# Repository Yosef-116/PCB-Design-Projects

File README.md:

# PCB Design Class — Semester Projects

This repository contains all the PCB design projects completed throughout my PCB Design course, created using **KiCad**. The projects progressively build on each other, covering fundamental circuit concepts from simple switching circuits to microcontroller-based systems, culminating in a full AC to DC power converter as the final project.

---

## Project 01 — Mini Inverter

A half-bridge DC inverter circuit built around the **IR2153 self-oscillating half-bridge driver** and two **N-Channel Power MOSFETs (17A, 60V, TO-220)**. The circuit drives a transformer to produce an AC-like output from a DC battery source. LEDs are used for status indication. This was the introductory project, covering basic switching topologies, MOSFET gate driving, and transformer-coupled power circuits.

**Key components:** IR2153, N-Channel MOSFETs, transformer, LED, battery

---

## Project 02 — Arduino Nano + LCD Display

A microcontroller-based project integrating an **Arduino Nano v3.x** with an **NHD-0420E2Z LCD display** (4×20 character). The board routes power, data lines, and passive components between the module and the display. This project introduced working with microcontroller modules in KiCad, footprint assignment for through-hole and SMD packages, and multi-component PCB layout.

**Key components:** Arduino Nano v3.x, NHD-0420E2Z LCD, resistors, capacitors, battery

---

## Project 03 — 4-Digit 7-Segment LED Display Driver

A display driver circuit built around the **CC56-12SRWA** — a 4-digit, 7-segment super bright red LED display (common cathode). The schematic routes the segment and digit control lines from a battery-powered source. This project focused on understanding multi-digit display multiplexing, current-limiting resistors for each segment, and organizing a moderately complex schematic cleanly.

**Key components:** CC56-12SRWA (4-digit 7-segment display), resistors, single-cell battery

---

## Project 05 — LED Sequencer (CD4017 + NE555 Timer)

A classic LED chaser/sequencer circuit using the **CD4017 Johnson Counter** (10 decoded outputs) driven by the **NE555 timer IC** configured in astable mode. The 555 generates a clock signal that steps the 4017 through its outputs sequentially, lighting one LED at a time in a running pattern. This project explored timer circuits, clocking logic ICs, and the fundamentals of sequential logic on a PCB.

**Key components:** CD4017B, NE555 (SOIC-8), LEDs, resistors, capacitors, single-cell battery

---

## Project 06 — Sound-Activated Relay (Clap Switch)

A sound-triggered switching circuit that uses an **ECM microphone (AOM-6545P-R)** to pick up audio signals, amplified by the **OPA27GP precision op-amp**. The amplified signal is processed by a **74LS109 Dual JK Flip-Flop** to toggle a **PR12 5V relay (SPDT)** via a **TIP122 NPN Darlington transistor**. A trimmer potentiometer sets the sensitivity threshold. This project brought together analog signal conditioning, digital logic, and electromechanical output on one board.

**Key components:** AOM-6545P-R ECM mic, OPA27GP op-amp, 74LS109 JK flip-flop, TIP122 Darlington transistor, PR12-5V-360-1C relay, 1N4001 flyback diode, trimmer potentiometer

---

## Project 07 — USB-C Powered LED Dimmer

A variable LED brightness circuit powered through a **USB Type-C receptacle (6-pin, power-only)**. The circuit uses a **BD140 PNP power transistor** as the main switch, a **TL431D shunt voltage regulator** for reference, and a **potentiometer (RK163)** to allow manual dimming control. A fast-switching diode (1N4148WT) handles transient protection. This project introduced USB-C power input integration and analog control of LED brightness through transistor biasing.

**Key components:** USB_C_Receptacle_PowerOnly_6P, BD140 PNP transistor, TL431D shunt regulator, RK163 potentiometer, 1N4148WT diode, LED, resistors

---

## Project 08 — Stereo Audio Amplifier (LA4440)

A two-channel stereo audio amplifier board built around the **LA4440-E**, a Class AB 2-channel amplifier IC in a 14-pin SIP package (by onsemi). The board includes the necessary input/output coupling capacitors and resistor network as specified in the datasheet. This project covered audio amplifier PCB layout considerations such as ground planes, decoupling, and heat dissipation for power ICs.

**Key components:** LA4440-E stereo amplifier IC (14-SIP), capacitors, resistors

---

## Final Project — AC to DC Power Supply Converter

The semester capstone project: a full **AC to DC rectifier and filter circuit** designed from scratch. The circuit takes an AC input through screw terminals, passes it through a **bridge rectifier built with four 1N4007 diodes** (1000V, 1A, DO-41), and smooths the output using **polarized electrolytic capacitors**. An LED with a current-limiting resistor serves as a power indicator. 

This project brought together everything learned in the course — schematic design, footprint assignment, PCB layout, design rule checks, Gerber file export, and board revision management.

**Key components:** 1N4007 rectifier diodes ×4 (bridge configuration), polarized electrolytic capacitors, resistor, LED, screw terminals (AC input / DC output)

---

## Tools Used

- **KiCad** — Schematic capture, PCB layout, Gerber export
- **Git** — Version control and project history

---

## Repository Structure

```
├── Project 01/           # Mini Inverter
├── Project_02/           # Arduino Nano + LCD Display
├── Project_03/           # 4-Digit 7-Segment Display
├── Project 05/           # LED Sequencer (4017 + 555)
├── PROJECT_06/           # Sound-Activated Relay
├── PROJECT_07/           # USB-C LED Dimmer
├── Project_08/           # Stereo Audio Amplifier
└── FINAL_PROJECT- AC to DC Converter/   # Full-Wave Rectifier Power Supply
```

Each folder contains the KiCad project files (`.kicad_sch`, `.kicad_pcb`, `.kicad_pro`), Gerber outputs where applicable, and automated KiCad backup archives.

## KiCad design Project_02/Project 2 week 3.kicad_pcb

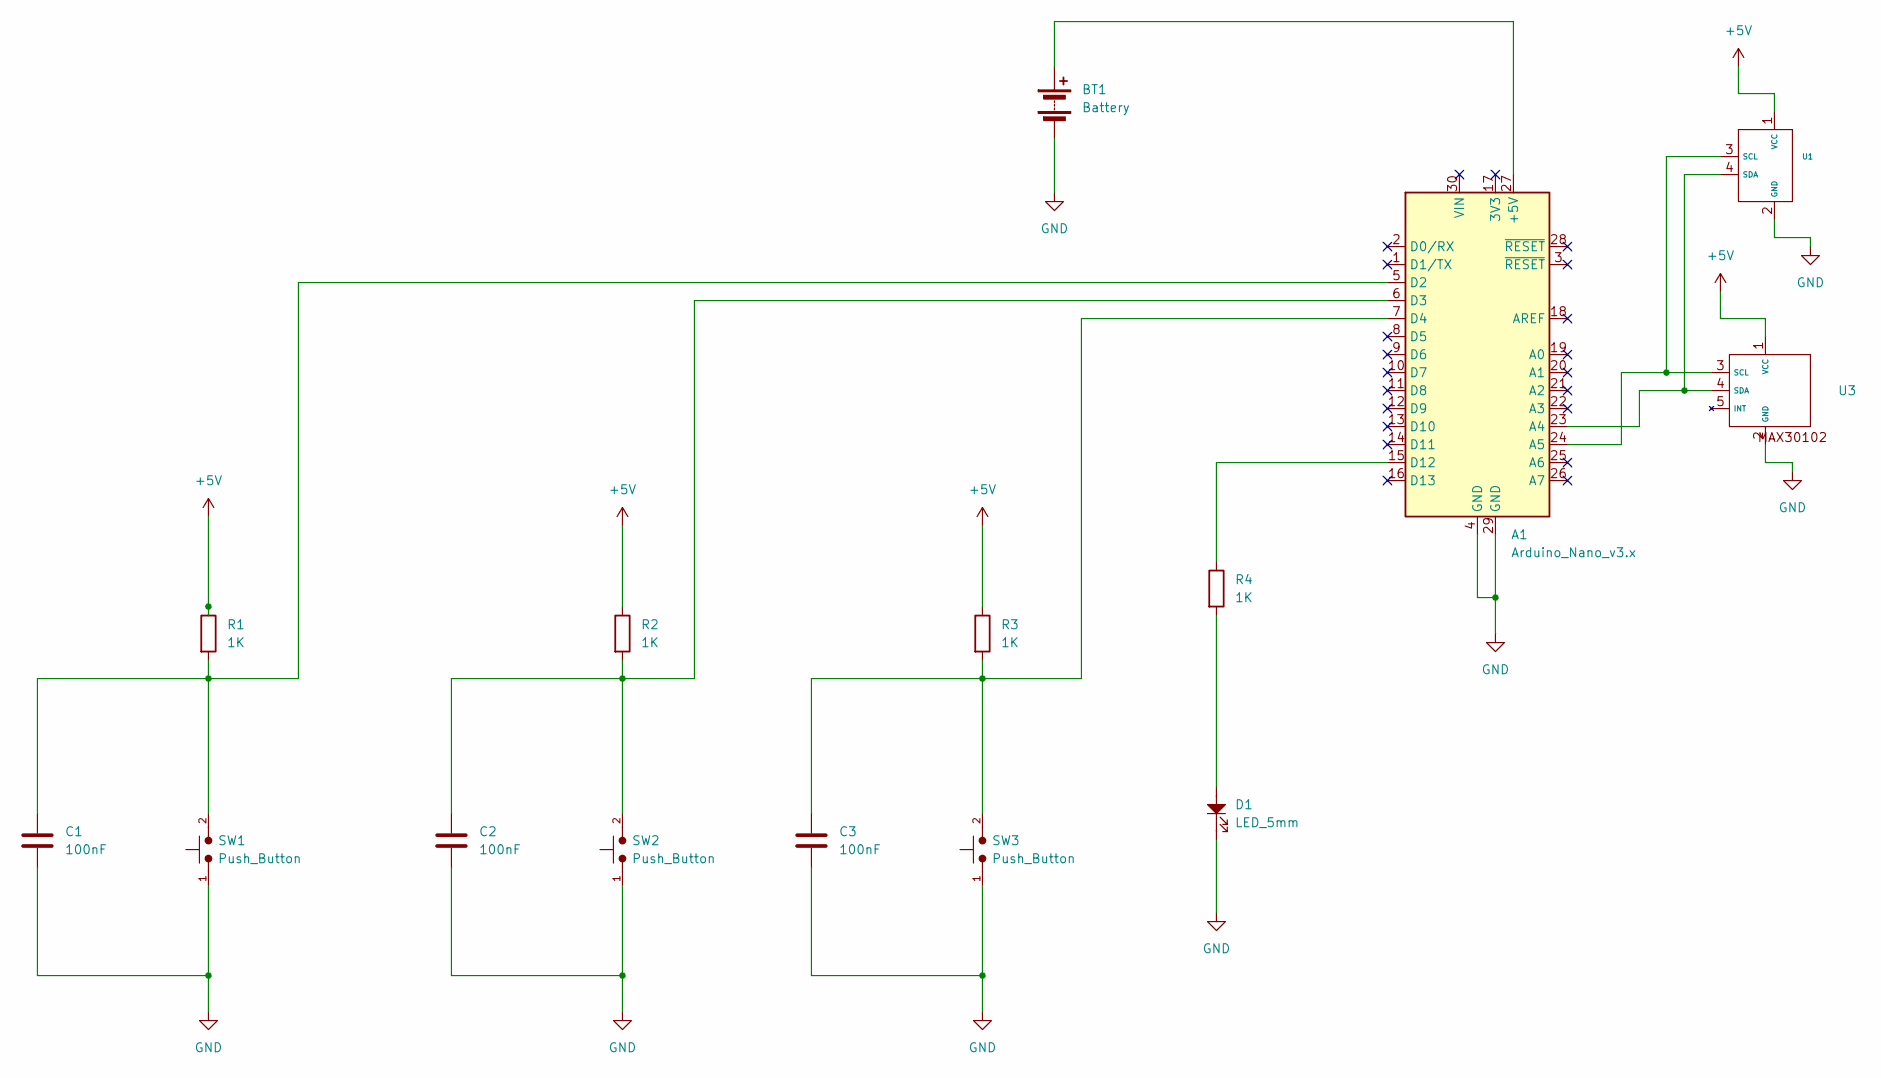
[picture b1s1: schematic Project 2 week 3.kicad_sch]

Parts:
A1: Arduino_Nano_v3.x; MODULE_ARDUINO_NANO
BT1: Battery; TerminalBlock_Xinya_XY308-2.54-3P_1x03_P2.54mm_Horizontal
C1, C2, C3: 100nF; CP_Radial_D6.3mm_P2.50mm
D1: LED_5mm; LED_D5.0mm
R1, R2, R3, R4: 1K; R_Axial_DIN0204_L3.6mm_D1.6mm_P5.08mm_Horizontal
SW1, SW2, SW3: Push_Button; SW_PUSH_6mm
U1: LCD_NHD-0420E2Z-FSW-GBW
U3: XDCR_MAX30101EFD_

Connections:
+5V: R1.1, R2.1, R3.1, U1.1 (VCC), U3.1 (VCC)
GND: A1.4 (GND), A1.29 (GND), BT1.2 (-), C1.2, C2.2, C3.2, D1.1, SW1.1, SW2.1, SW3.1, U1.2 (GND), U3.2 (GND)
unnamed: A1.27 (+5V), BT1.1 (+)
unnamed: A1.23 (A4), U1.4 (SDA), U3.4 (SDA)
unnamed: A1.24 (A5), U1.3 (SCL), U3.3 (SCL)
unnamed: A1.5 (D2), C1.1, R1.2, SW1.2
unnamed: A1.6 (D3), C2.1, R2.2, SW2.2
unnamed: A1.7 (D4), C3.1, R3.2, SW3.2
unnamed: A1.15 (D12), R4.1
unnamed: D1.2, R4.2

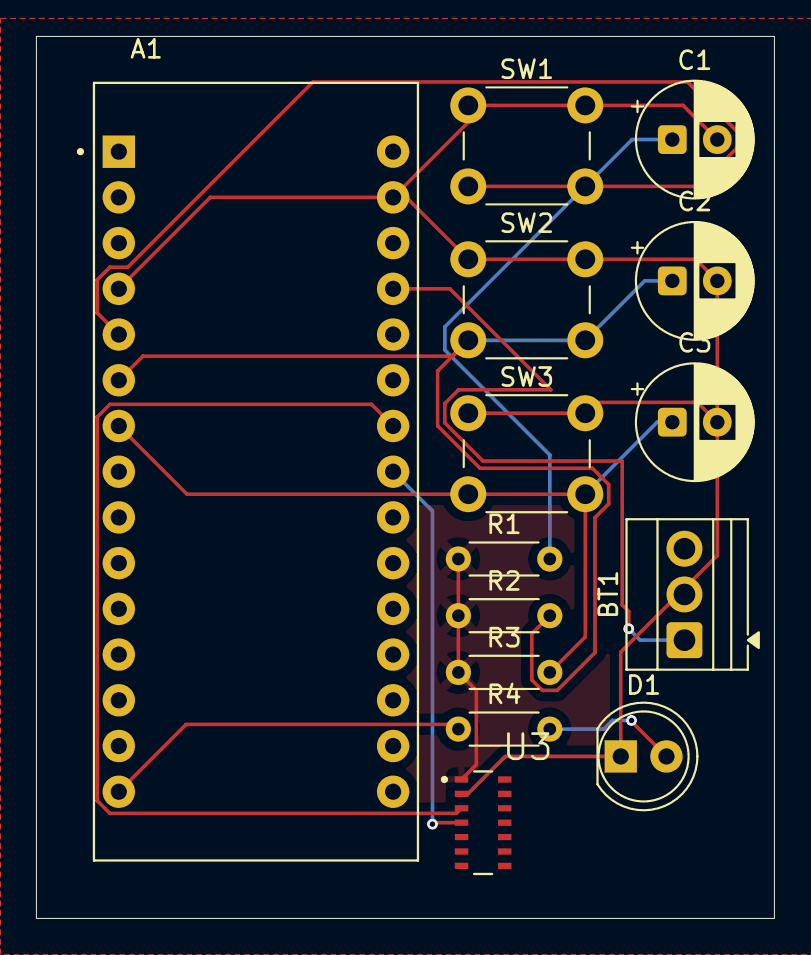
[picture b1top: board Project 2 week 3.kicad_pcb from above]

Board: 2 copper layers, 41.0 x 49.0 mm, 14 parts (0 on the bottom side), 10 nets.

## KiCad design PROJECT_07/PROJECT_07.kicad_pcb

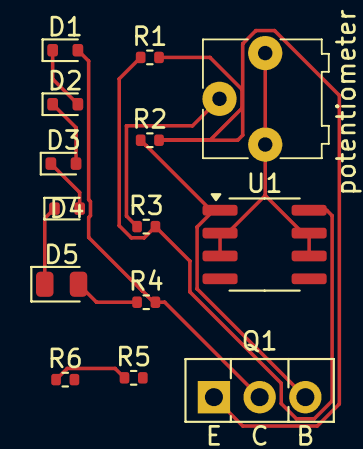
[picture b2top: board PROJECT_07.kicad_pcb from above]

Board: 2 copper layers, 14 parts (0 on the bottom side), 12 nets.

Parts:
D1, D2, D3, D4: 1N4148WT; D_SOD-523
D5: LED; LED_0805_2012Metric
Q1: BD140; TO-126-3_Vertical_ECB
R1, R2, R3, R4, R5, R6: Resistor; R_0402_1005Metric
RV1: potentiometer; potentiometer_3362P
U1: TL431D; SOIC-8_3.9x4.9mm_P1.27mm

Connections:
GND: R5.1, R6.1
unnamed: Q1.1 (E), R1.2, R2.2
unnamed: D4.1 (K), D5.1
unnamed: D1.2 (A), Q1.2 (C), R4.2
unnamed: D1.1 (K), D2.2 (A)
unnamed: D2.1 (K), D3.2 (A)
unnamed: D3.1 (K), D4.2 (A)
unnamed: D5.2, R4.1
unnamed: Q1.3 (B), R2.1, U1.1 (K)
unnamed: R3.1, RV1.1
unnamed: RV1.2, RV1.3, U1.2 (A), U1.3 (A), U1.6 (A), U1.7 (A)
unnamed: R1.1, R3.2, U1.8 (REF)

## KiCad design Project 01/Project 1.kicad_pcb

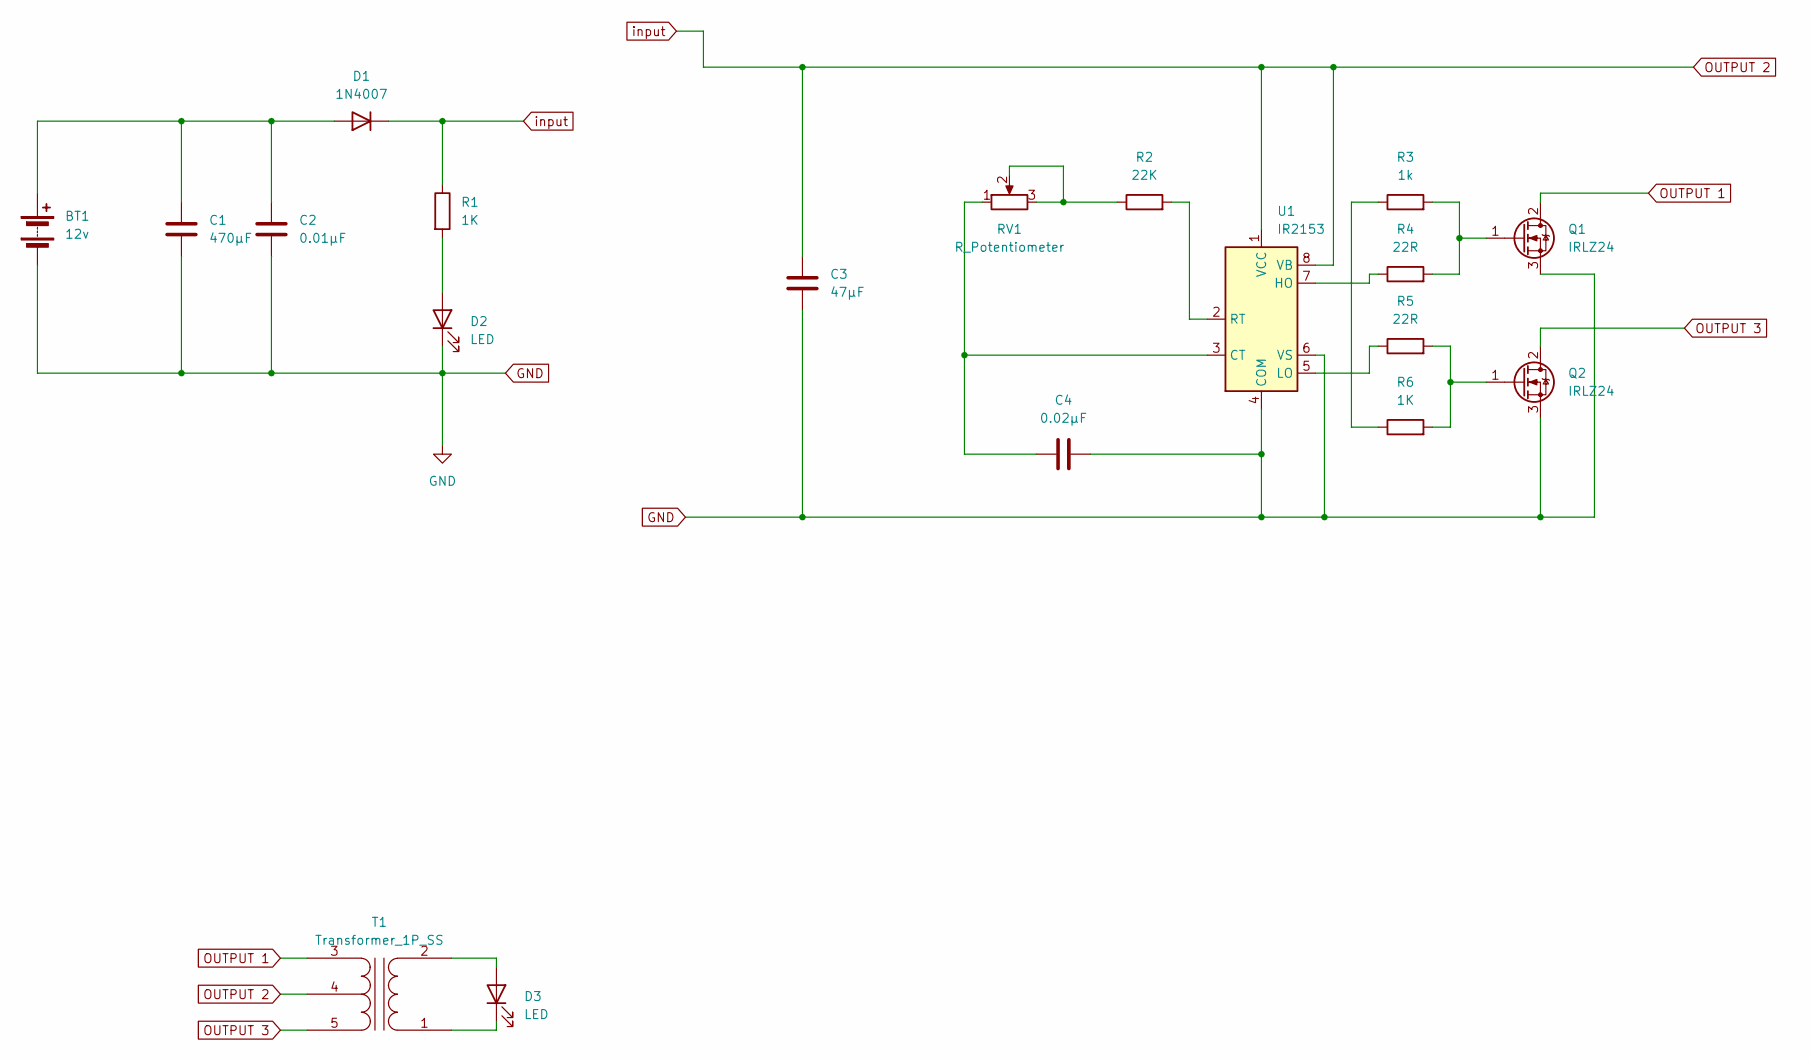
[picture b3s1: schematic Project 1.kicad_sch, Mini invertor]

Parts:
BT1: 12v; TerminalBlock_Xinya_XY308-2.54-2P_1x02_P2.54mm_Horizontal
C1: 470µF; CP_Radial_D6.3mm_P2.50mm
C2: 0.01µF; C_Disc_D3.0mm_W1.6mm_P2.50mm
C3: 47µF; CP_Radial_D5.0mm_P2.50mm
C4: 0.02µF; C_Disc_D3.0mm_W2.0mm_P2.50mm
D1: 1N4007; D_DO-41_SOD81_P10.16mm_Horizontal
D2: LED; TerminalBlock_Xinya_XY308-2.54-2P_1x02_P2.54mm_Horizontal
D3: LED; LED_D5.0mm
Q1, Q2: IRLZ24; TO-220-3_Vertical
R1, R6: 1K; R_Axial_DIN0204_L3.6mm_D1.6mm_P5.08mm_Horizontal
R2: 22K; R_Axial_DIN0204_L3.6mm_D1.6mm_P5.08mm_Horizontal
R3: 1k; R_Axial_DIN0204_L3.6mm_D1.6mm_P5.08mm_Horizontal
R4, R5: 22R; R_Axial_DIN0204_L3.6mm_D1.6mm_P5.08mm_Horizontal
RV1: R_Potentiometer; Potentiometer_ACP_CA6-H2,5_Horizontal
T1: Transformer_1P_SS; TerminalBlock_Xinya_XY308-2.54-5P_1x05_P2.54mm_Horizontal
U1: IR2153; DIP-8_W7.62mm

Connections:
GND: BT1.2 (-), C1.2, C2.2, C3.2, C4.2, D2.1 (K), Q1.3 (S), Q2.3 (S), U1.4 (COM), U1.6 (VS)
unnamed: BT1.1 (+), C1.1, C2.1, D1.2 (A)
unnamed: D2.2 (A), R1.2
unnamed: D3.2 (A), T1.2 (AB)
unnamed: D3.1 (K), T1.1 (AA)
unnamed: Q1.1 (G), R3.2, R4.2
unnamed: Q2.1 (G), R5.2, R6.2
unnamed: R2.1, RV1.2, RV1.3
unnamed: R3.1, R6.1
unnamed: C4.1, RV1.1, U1.3 (CT)
unnamed: R4.1, U1.7 (HO)
unnamed: R5.1, U1.5 (LO)
unnamed: R2.2, U1.2 (RT)
OUTPUT 1: Q1.2 (D), T1.3 (SA)
OUTPUT 2: C3.1, D1.1 (K), R1.1, T1.4 (SC), U1.1 (VCC), U1.8 (VB)
OUTPUT 3: Q2.2 (D), T1.5 (SB)

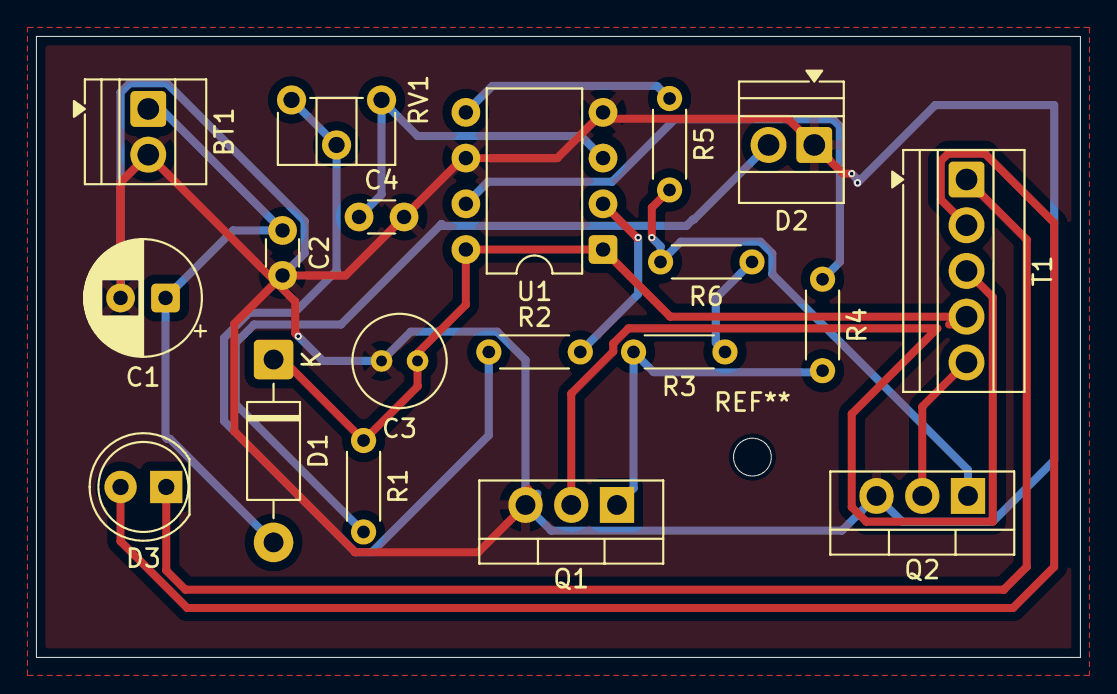
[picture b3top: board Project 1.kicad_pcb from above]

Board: 2 copper layers, 58.0 x 34.5 mm, 19 parts (0 on the bottom side), 16 nets.

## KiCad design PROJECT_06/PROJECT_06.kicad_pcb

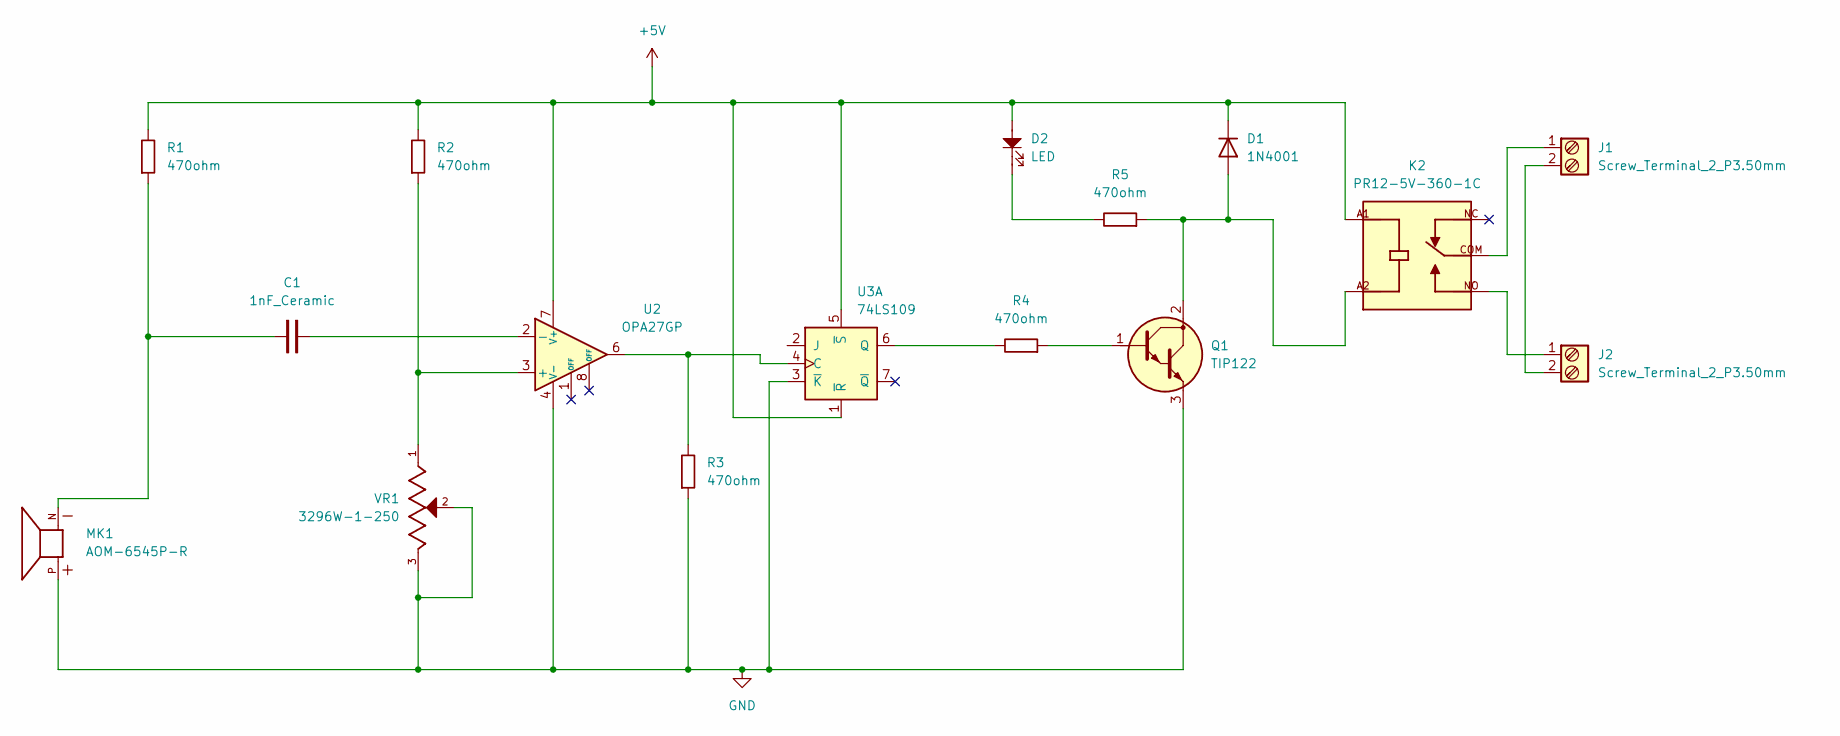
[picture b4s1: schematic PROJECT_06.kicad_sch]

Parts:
C1: 1nF_Ceramic; C_Disc_D5.0mm_W2.5mm_P2.50mm
D1: 1N4001; D_DO-41_SOD81_P10.16mm_Horizontal
D2: LED; LED_D5.0mm
J1, J2: Screw_Terminal_2_P3.50mm; TerminalBlock_Phoenix_PT-1,5-2-3.5-H_1x02_P3.50mm_Horizontal
K2: PR12-5V-360-1C; RELAY_PR12-5V-360-1C; PARTREV 1.0
MK1: AOM-6545P-R; MIC_AOM-6545P-R; PARTREV D
Q1: TIP122; TO-220-3_Vertical_BCE
R1, R2, R3, R4, R5: 470ohm; R_Axial_DIN0207_L6.3mm_D2.5mm_P10.16mm_Horizontal
U2: OPA27GP; DIP-8_W7.62mm_LongPads
U3: 74LS109; DIP794W45P254L959H508Q8
VR1: 3296W-1-250; TRIM_3296W-1-250; PARTREV 05/16

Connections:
+5V: D1.1 (K), D2.2, K2.A1, R1.2, R2.2, U2.7 (V+), U3.1 (~R), U3.5 (~S)
GND: MK1.P, Q1.3 (E), R3.1, U2.4 (V-), U3.3 (~K), VR1.2, VR1.3
unnamed: C1.1, MK1.N, R1.1
unnamed: D1.2 (A), K2.A2, Q1.2 (C), R5.1
unnamed: D2.1, R5.2
unnamed: J1.1, K2.COM
unnamed: J1.2, J2.2
unnamed: J2.1, K2.NO
unnamed: Q1.1 (B), R4.1
unnamed: R2.1, U2.3 (+), VR1.1
unnamed: C1.2, U2.2 (-)
unnamed: R3.2, U2.6, U3.4 (C)
unnamed: R4.2, U3.6 (Q)

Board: 4 copper layers, 16 parts (0 on the bottom side), 13 nets, no tracks yet.

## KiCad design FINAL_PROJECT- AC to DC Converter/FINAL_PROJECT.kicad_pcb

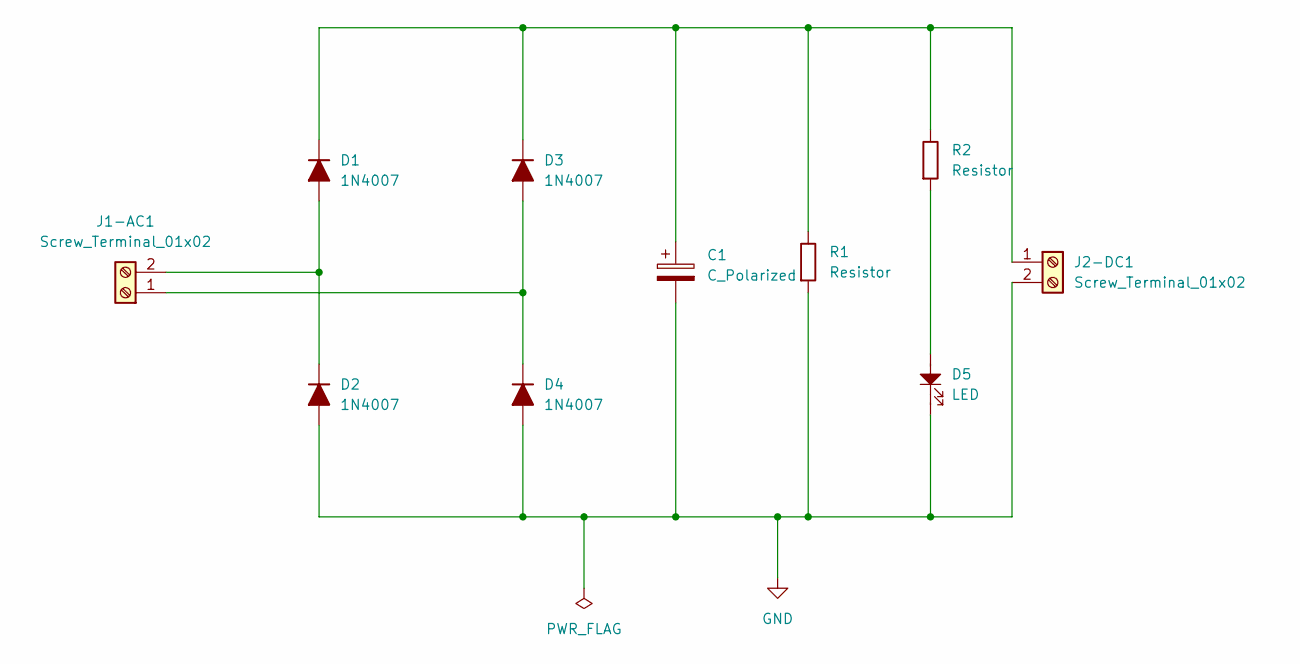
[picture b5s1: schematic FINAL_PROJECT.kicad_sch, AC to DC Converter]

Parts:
C1: C_Polarized; CP_Radial_D10.0mm_P5.00mm
D1, D2, D3, D4: 1N4007; D_DO-41_SOD81_P7.62mm_Horizontal
D5: LED; LED_D5.0mm
J1-AC1, J2-DC1: Screw_Terminal_01x02; TerminalBlock_Xinya_XY308-2.54-2P_1x02_P2.54mm_Horizontal
R1, R2: Resistor; R_Axial_DIN0207_L6.3mm_D2.5mm_P10.16mm_Horizontal

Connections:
GND: C1.2, D2.2 (A), D4.2 (A), D5.1, J2-DC1.2, R1.1
unnamed: D1.2 (A), D2.1 (K), J1-AC1.2
unnamed: C1.1, D1.1 (K), D3.1 (K), J2-DC1.1, R1.2, R2.2
unnamed: D3.2 (A), D4.1 (K), J1-AC1.1
unnamed: D5.2, R2.1

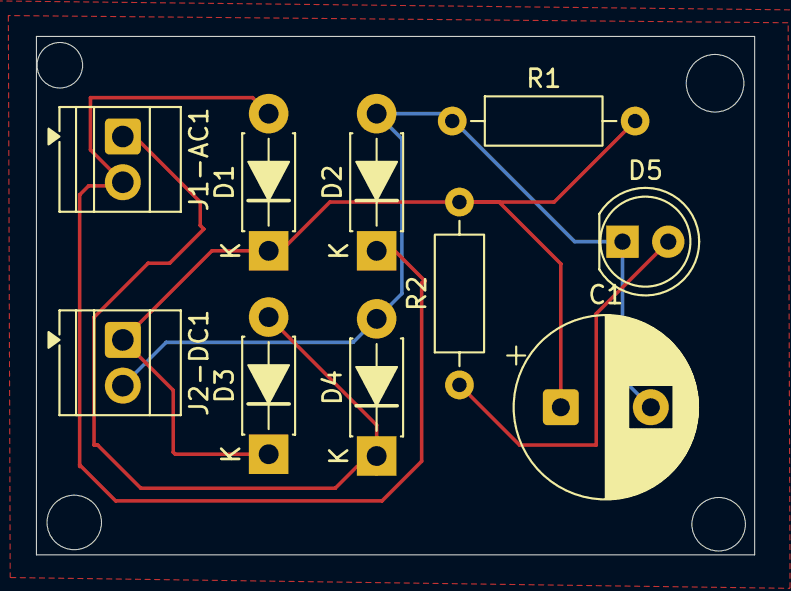
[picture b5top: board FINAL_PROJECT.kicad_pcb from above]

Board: 2 copper layers, 39.9 x 28.8 mm, 10 parts (0 on the bottom side), 5 nets.

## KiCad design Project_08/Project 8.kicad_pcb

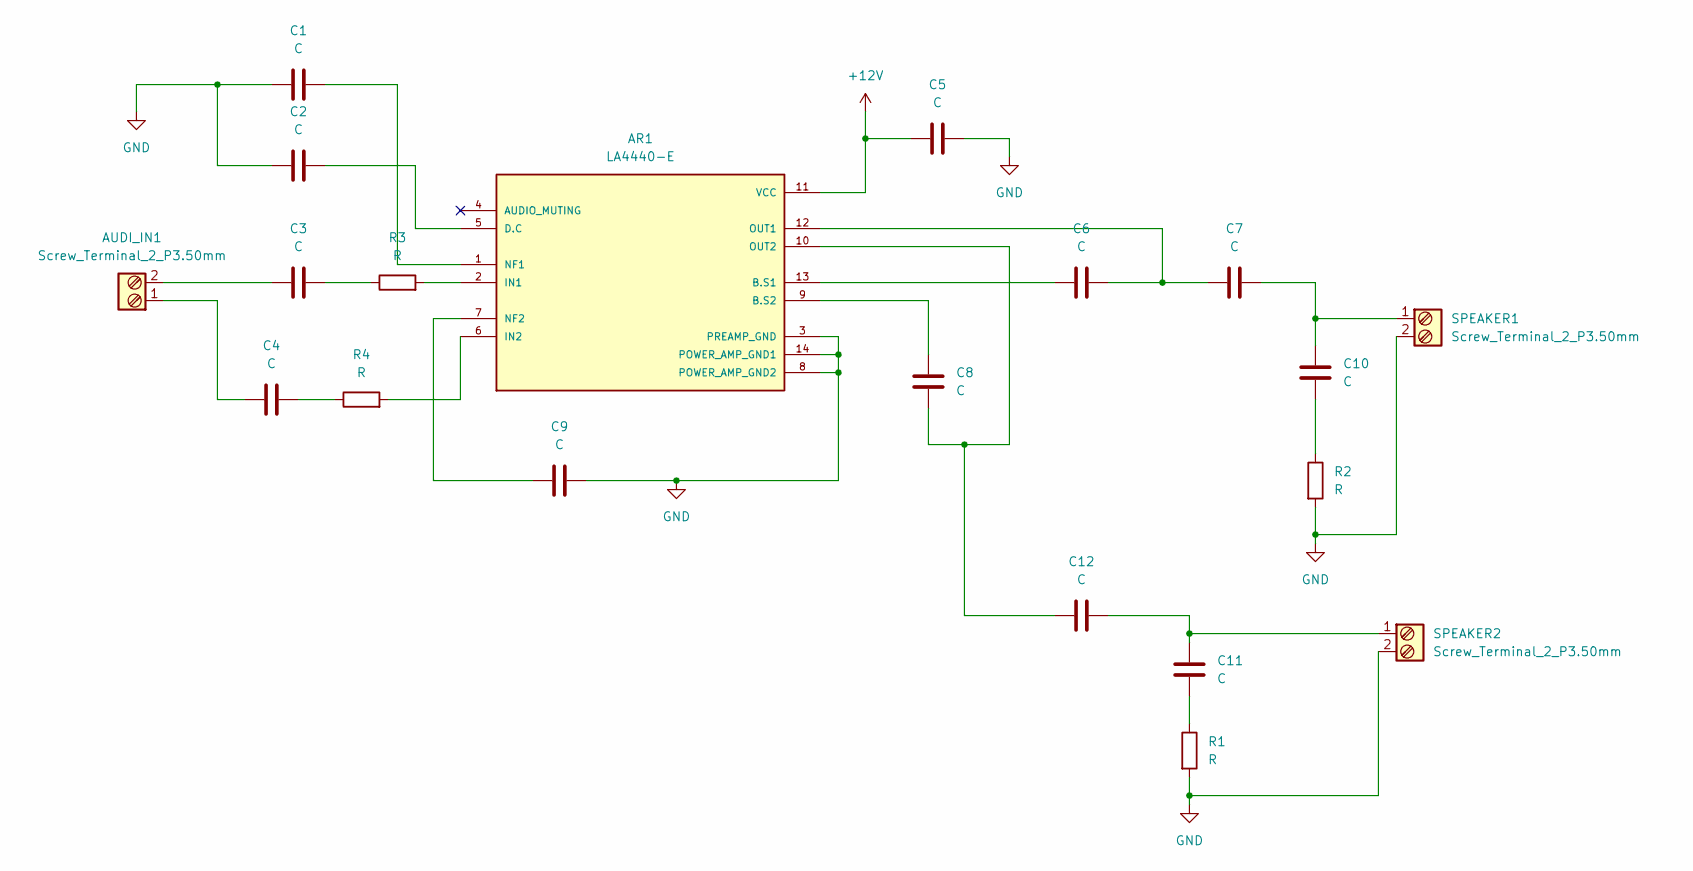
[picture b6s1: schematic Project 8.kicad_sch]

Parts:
AR1: LA4440-E; SIP460W60P254L3690H1500Q14; PARTREV 23 Oct 2013
AUDI_IN1: Screw_Terminal_2_P3.50mm; TerminalBlock_Phoenix_PT-1,5-2-3.5-H_1x02_P3.50mm_Horizontal
C1, C2, C3, C4, C10, C11: C; CP_Radial_D5.0mm_P2.50mm
C5, C6: C; C_Disc_D3.0mm_W2.0mm_P2.50mm
C7, C8: C; CP_Radial_D10.0mm_P5.00mm
C9: C; CP_Radial_D8.0mm_P3.50mm
C12: C; CP_Radial_D8.0mm_P5.00mm
R1, R2, R3, R4: R; R_Axial_DIN0207_L6.3mm_D2.5mm_P7.62mm_Horizontal
SPEAKER1, SPEAKER2: Screw_Terminal_2_P3.50mm; TerminalBlock_Phoenix_PT-1,5-2-3.5-H_1x02_P3.50mm_Horizontal

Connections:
+12V: AR1.11 (VCC), C5.1
GND: AR1.3 (PREAMP_GND), AR1.8 (POWER_AMP_GND2), AR1.14 (POWER_AMP_GND1), C1.1, C2.1, C5.2, C9.2, R1.2, R2.2, SPEAKER1.2, SPEAKER2.2
unnamed: AR1.13 (B.S1), C6.1
unnamed: AR1.9 (B.S2), C8.2
unnamed: AR1.5 (D.C), C2.2
unnamed: AR1.2 (IN1), R3.2
unnamed: AR1.6 (IN2), R4.2
unnamed: AR1.1 (NF1), C1.2
unnamed: AR1.7 (NF2), C9.1
unnamed: AR1.12 (OUT1), C6.2, C7.1
unnamed: AR1.10 (OUT2), C8.1, C12.2
unnamed: AUDI_IN1.1, C4.1
unnamed: AUDI_IN1.2, C3.1
unnamed: C3.2, R3.1
unnamed: C4.2, R4.1
unnamed: C10.1, R2.1
unnamed: C7.2, C10.2, SPEAKER1.1
unnamed: C11.1, R1.1
unnamed: C11.2, C12.1, SPEAKER2.1

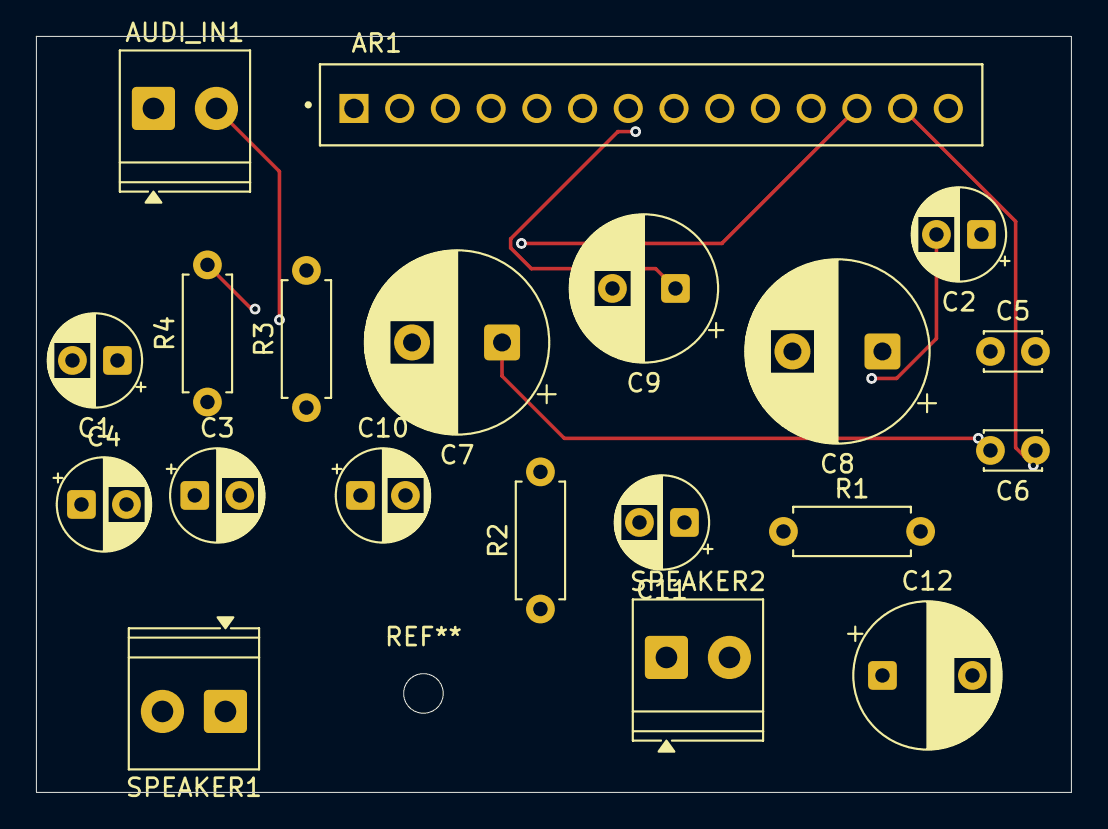
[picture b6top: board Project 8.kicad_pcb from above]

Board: 4 copper layers, 57.5 x 42.0 mm, 20 parts (0 on the bottom side), 19 nets.

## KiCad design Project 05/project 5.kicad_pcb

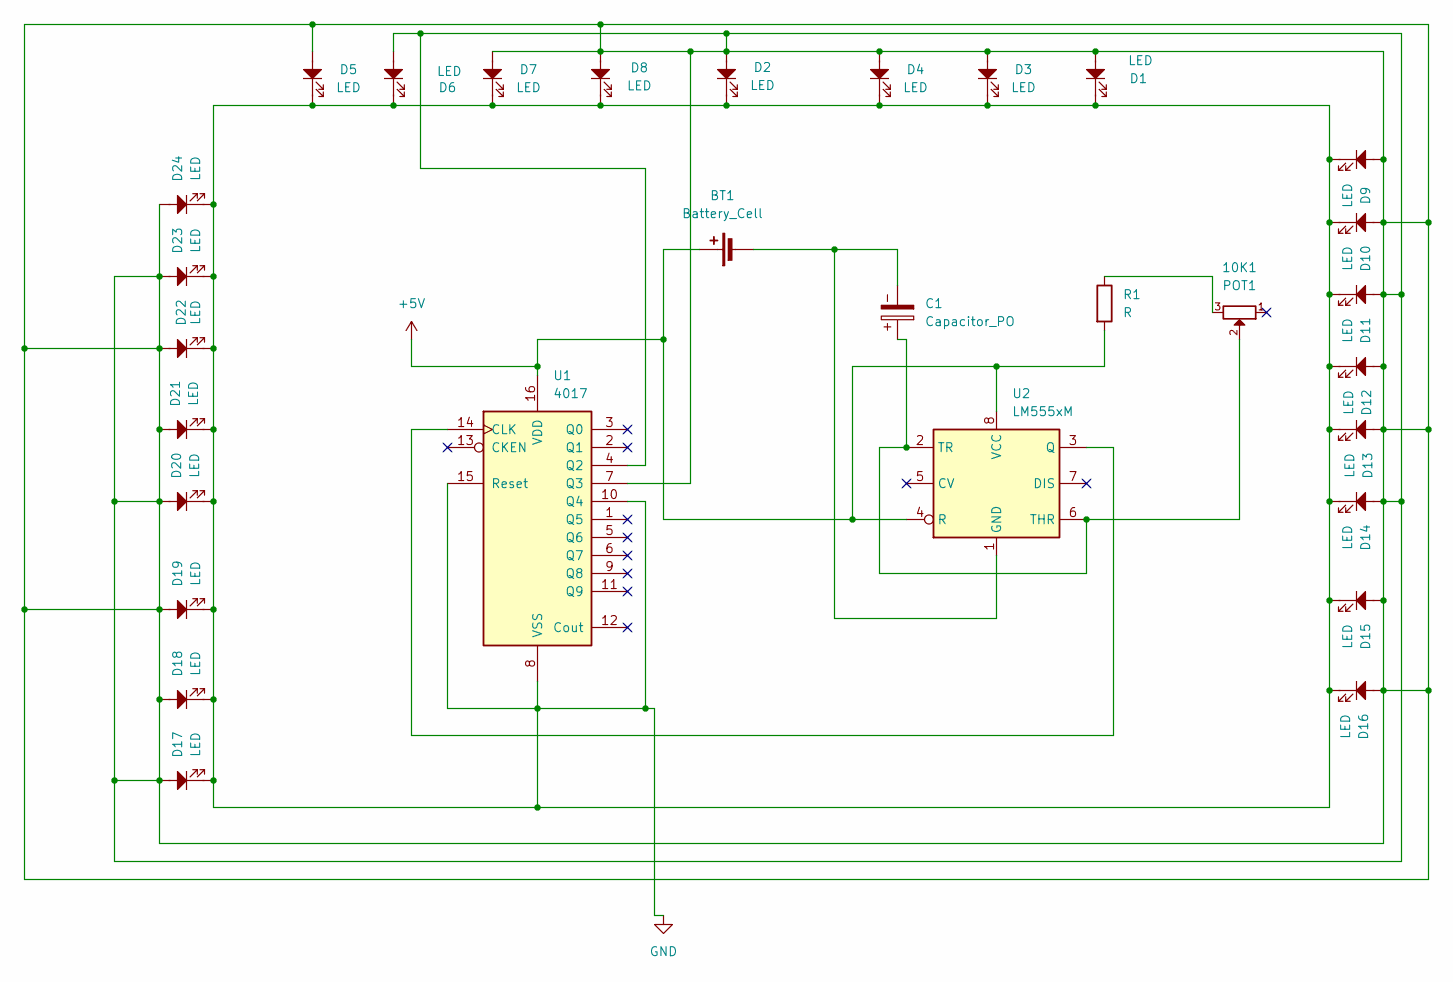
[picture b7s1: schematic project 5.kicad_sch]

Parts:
10K1: POT1; Potentiometer_Alps_RK163_Single_Horizontal
BT1: Battery_Cell; TerminalBlock_Xinya_XY308-2.54-2P_1x02_P2.54mm_Horizontal
C1: Capacitor_PO; CP_Radial_D5.0mm_P2.50mm
D1, D2, D3, D4, D5, D6, D7, D8, D9, D10, D11, D12, D13, D14, D15, D16, D17, D18, D19, D20, D21, D22, D23, D24: LED; LED_D5.0mm
R1: R; R_Axial_DIN0207_L6.3mm_D2.5mm_P7.62mm_Horizontal
U1: 4017; DIP794W45P254L1969H508Q16
U2: LM555xM; SOIC-8_3.9x4.9mm_P1.27mm

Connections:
+5V: BT1.1 (+), R1.2, U1.16 (VDD), U2.4 (R), U2.8 (VCC)
GND: D1.1, D2.1, D3.1, D4.1, D5.1, D6.1, D7.1, D8.1, D9.1, D10.1, D11.1, D12.1, D13.1, D14.1, D15.1, D16.1, D17.1, D18.1, D19.1, D20.1, D21.1, D22.1, D23.1, D24.1, U1.8 (VSS), U1.10 (Q4), U1.15 (Reset)
unnamed: 10K1.3, R1.1
unnamed: BT1.2 (-), C1.2, U2.1 (GND)
unnamed: U1.14 (CLK), U2.3 (Q)
unnamed: D1.2, D2.2, D3.2, D4.2, D5.2, D6.2, D7.2, D8.2, D9.2, D10.2, D11.2, D12.2, D13.2, D14.2, D15.2, D16.2, D17.2, D18.2, D19.2, D20.2, D21.2, D22.2, D23.2, D24.2, U1.4 (Q2), U1.7 (Q3)
unnamed: 10K1.2, C1.1, U2.2 (TR), U2.6 (THR)

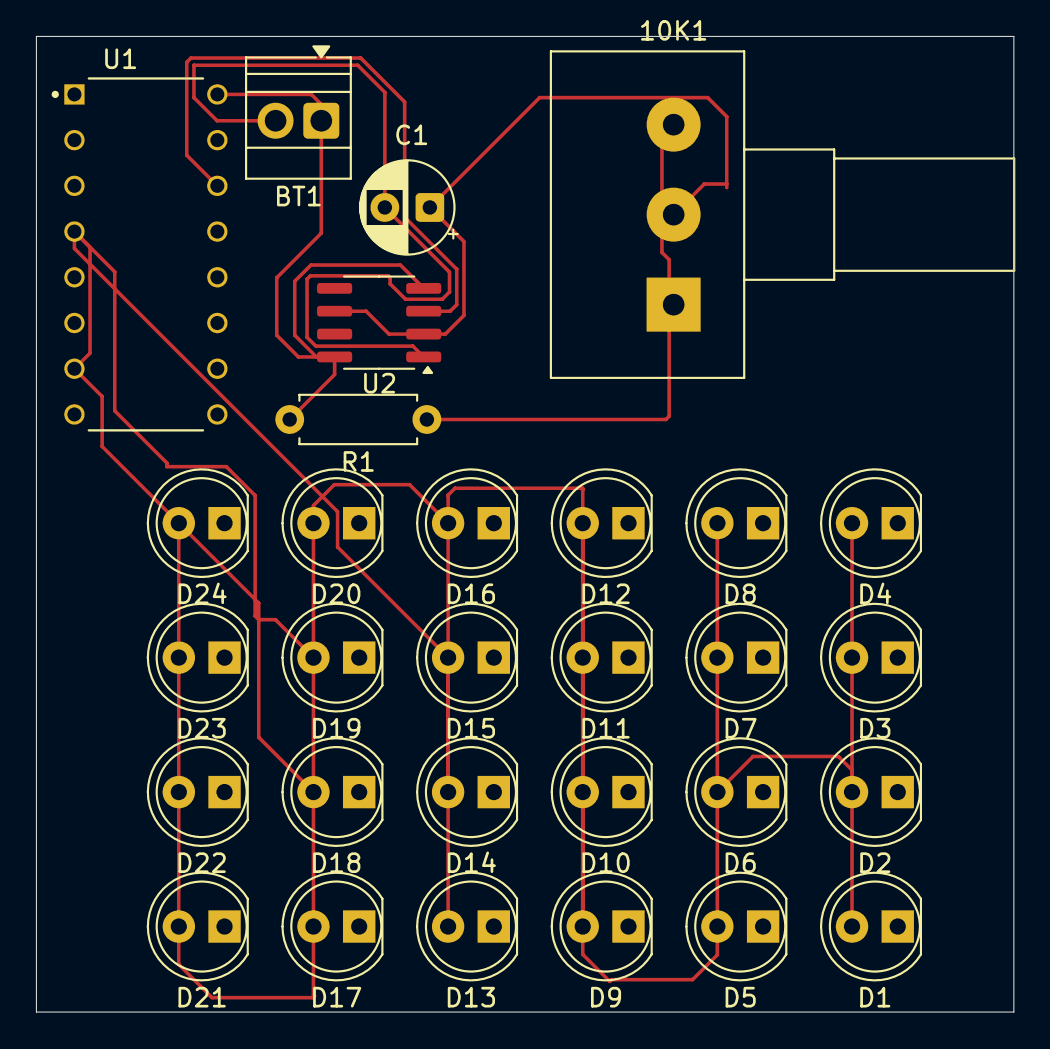
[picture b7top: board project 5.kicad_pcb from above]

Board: 4 copper layers, 54.3 x 54.2 mm, 30 parts (0 on the bottom side), 7 nets.

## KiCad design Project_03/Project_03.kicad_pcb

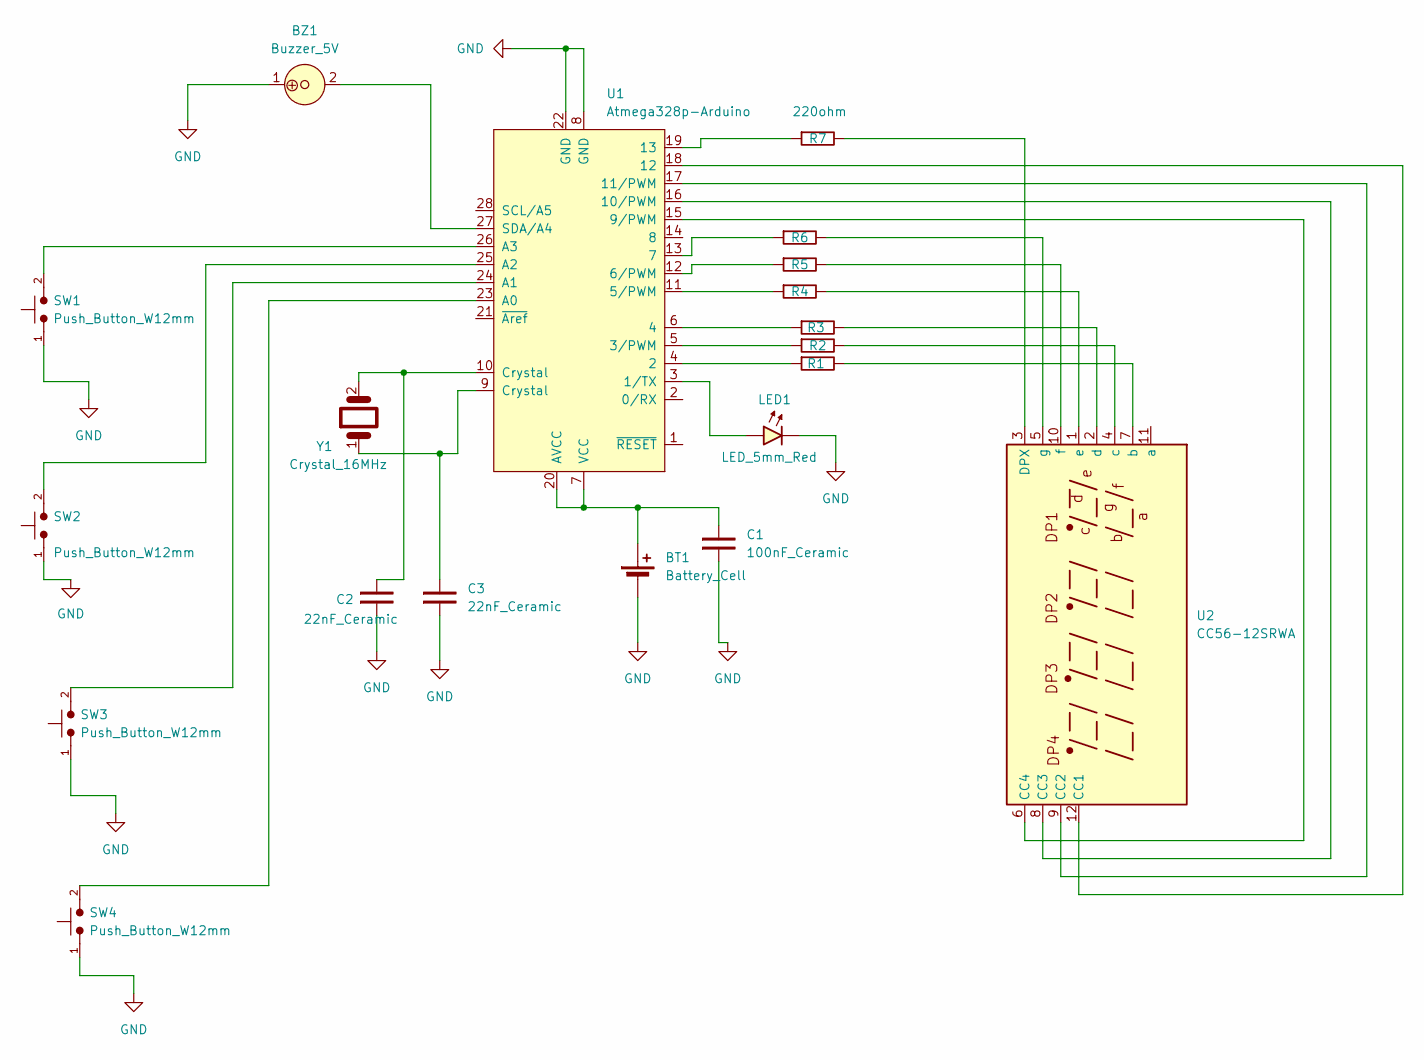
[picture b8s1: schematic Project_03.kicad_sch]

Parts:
BT1: Battery_Cell; TerminalBlock_Xinya_XY308-2.54-2P_1x02_P2.54mm_Horizontal
BZ1: Buzzer_5V; MagneticBuzzer_ProSignal_ABT-410-RC
C1: 100nF_Ceramic; C_Disc_D5.0mm_W2.5mm_P2.50mm
C2, C3: 22nF_Ceramic; C_Disc_D5.0mm_W2.5mm_P2.50mm
LED1: LED_5mm_Red; LED_D5.0mm
R1, R2, R3, R4, R5, R6, R7: 220ohm; R_Axial_DIN0207_L6.3mm_D2.5mm_P10.16mm_Horizontal
SW1, SW2, SW3, SW4: Push_Button_W12mm; SW_PUSH_6mm
U1: Atmega328p-Arduino; DIP-28_W7.62mm_LongPads
U2: CC56-12SRWA; CA56-12SRWA
Y1: Crystal_16MHz; Crystal_HC49-4H_Vertical

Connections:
GND: BT1.2 (-), BZ1.1, C1.1, C2.1, C3.1, LED1.1 (K), SW1.1, SW2.1, SW3.1, SW4.1, U1.8 (GND), U1.22 (GND)
unnamed: BT1.1 (+), C1.2, U1.7 (VCC), U1.20 (AVCC)
unnamed: C2.2, U1.10 (Crystal), Y1.2
unnamed: C3.2, U1.9 (Crystal), Y1.1
unnamed: LED1.2 (A), U1.3 (1/TX)
unnamed: R1.1, U1.4 (2)
unnamed: R2.1, U1.5 (3/PWM)
unnamed: R3.1, U1.6 (4)
unnamed: R4.1, U1.11 (5/PWM)
unnamed: R5.1, U1.12 (6/PWM)
unnamed: R6.1, U1.13 (7)
unnamed: U1.15 (9/PWM), U2.6 (CC4)
unnamed: U1.16 (10/PWM), U2.8 (CC3)
unnamed: U1.17 (11/PWM), U2.9 (CC2)
unnamed: U1.18 (12), U2.12 (CC1)
unnamed: R7.1, U1.19 (13)
unnamed: SW4.2, U1.23 (A0)
unnamed: SW3.2, U1.24 (A1)
unnamed: SW2.2, U1.25 (A2)
unnamed: SW1.2, U1.26 (A3)
unnamed: BZ1.2, U1.27 (SDA/A4)
unnamed: R7.2, U2.3 (DPX)
unnamed: R1.2, U2.7 (b)
unnamed: R2.2, U2.4 (c)
unnamed: R3.2, U2.2 (d)
unnamed: R4.2, U2.1 (e)
unnamed: R5.2, U2.10 (f)
unnamed: R6.2, U2.5 (g)
